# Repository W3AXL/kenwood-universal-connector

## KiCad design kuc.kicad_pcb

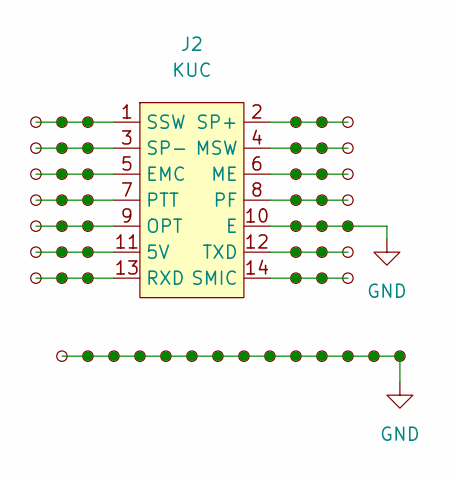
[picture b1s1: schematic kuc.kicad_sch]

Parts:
J2: KUC; KUC_FP
TP1, TP2, TP3, TP4, TP5, TP6, TP7, TP8, TP9, TP10, TP11, TP12, TP13, TP14, TP15, TP16, TP17, TP18, TP19, TP20, TP21, TP22, TP23, TP24, TP25, TP26, TP27, TP28, TP29, TP30, TP31, TP32, TP33, TP34, TP35, TP36, TP37, TP38, TP39, TP40, TP41, TP42, TP43, TP44, TP45, TP46, TP47, TP48, TP49, TP50, TP51, TP52, TP53, TP54, TP55, TP56: TestPoint_Small; TestPoint_THTPad_D1.0mm_Drill0.5mm

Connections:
GND: J2.10 (E), TP26.1, TP33.1, TP40.1, TP43.1, TP44.1, TP45.1, TP46.1, TP47.1, TP48.1, TP49.1, TP50.1, TP51.1, TP52.1, TP53.1, TP54.1, TP55.1, TP56.1; also elsewhere on the board
unnamed: J2.1 (SSW), TP1.1, TP8.1, TP15.1
unnamed: J2.2 (SP+), TP22.1, TP29.1, TP36.1
unnamed: J2.3 (SP-), TP2.1, TP9.1, TP16.1
unnamed: J2.4 (MSW), TP23.1, TP30.1, TP37.1
unnamed: J2.5 (EMC), TP3.1, TP10.1, TP17.1
unnamed: J2.6 (ME), TP24.1, TP31.1, TP38.1
unnamed: J2.7 (PTT), TP4.1, TP11.1, TP18.1
unnamed: J2.8 (PF), TP25.1, TP32.1, TP39.1
unnamed: J2.9 (OPT), TP5.1, TP12.1, TP19.1
unnamed: J2.11 (5V), TP6.1, TP13.1, TP20.1
unnamed: J2.12 (TXD), TP27.1, TP34.1, TP41.1
unnamed: J2.13 (RXD), TP7.1, TP14.1, TP21.1
unnamed: J2.14 (SMIC), TP28.1, TP35.1, TP42.1

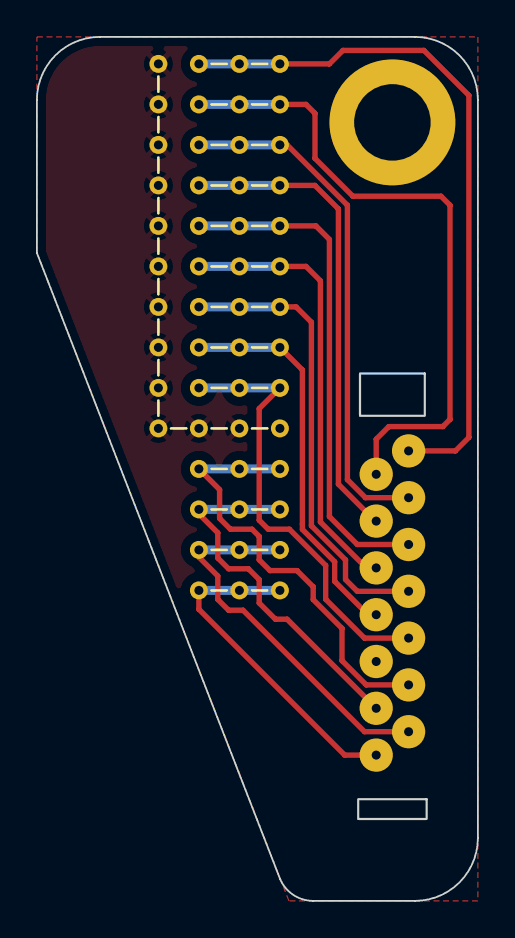
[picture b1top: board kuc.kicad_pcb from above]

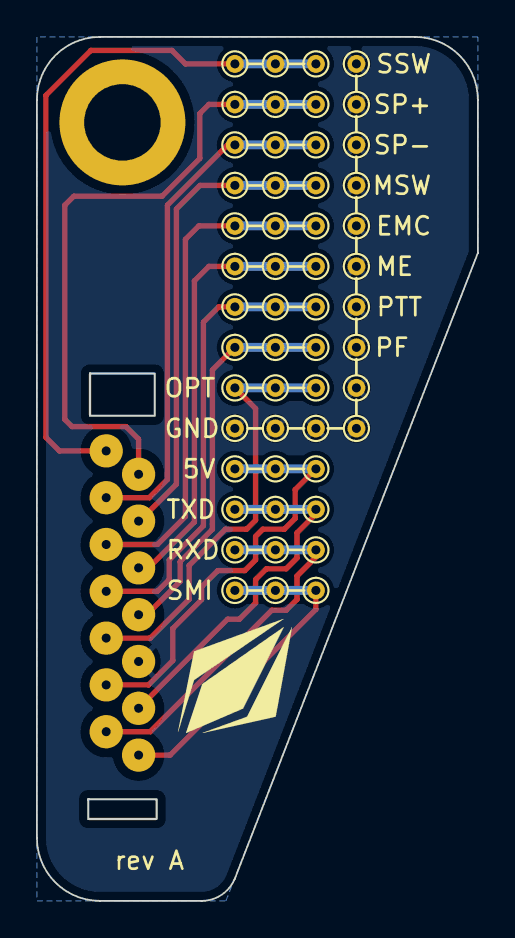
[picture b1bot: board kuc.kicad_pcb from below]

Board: 2 copper layers, 24.5 x 48.0 mm, 53 parts (53 on the bottom side), 14 nets.

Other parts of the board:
TPe: TestPoint_Small; TestPoint_THTPad_D1.0mm_Drill0.5mm

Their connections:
GND: TPe.1; also elsewhere on the board

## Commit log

2023-05-29 initial design commit
2023-05-29 added schematic details
2023-05-29 added STLs for connector housing
